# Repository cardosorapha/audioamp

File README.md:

# Amplificador de Audio

Essa é uma placa contendo um filtro passa-baixas de terceira ordem de Chebyshev com um amplificador de áudio baseado no TDA2030. No [esquemático](./Esquemático.pdf), as conexões estão descritas e separadas em blocos, que fizeram parte do projeto da [PCB](./PCB.pdf). Para montar o projeto, uma lista de materiais interativa está disponível [aqui](https://cardosorapha.github.io/audioamp/).

## Uso

Esse circuito recebe um sinal como entrada, dá um ganho o filtra com as seguintes especificações

* fs1 = 1200Hz
* fp1 = 4200hz
* Amin = 40dB
* Amax = 2dB
* Gcc = 0.5V/V

O sinal filtrado segue para o amplificador que suporta cargas de até 8R. 

### Alimentação

* +14V indicado por +VDC
* -14V indicado por -VDC
* GND

### Entradas

* Sinal de áudio indicado por por +SIG
* GND

### Saídas

* OUT1
* OUT2

Devem ser conectados ao speaker.

### Fabricação

Os arquivos gerber estão disponíveis na pasta [gerber](./gerber) para fabricação. 

## Customização

Pré-requisitos:
* [KiCAD](https://kicad-pcb.org/)

O projeto pode ser facilmente clonado com:
```
git clone https://github.com/cardosorapha/audioamp.git
```

Qualquer filtro passa-baixas de terceira ordem de topologia Sallen-Key pode ser implementado sem nenhuma modificação na placa, apenas nos componentes. Com isso, é possível modificar seus parâmetros facilmente, adaptando-os para a aplicação.

## Contato

Raphael Cardoso - cardosodeoliveir@gmail.com

Link do Projeto: [https://github.com/cardosorapha/audioamp](https://github.com/cardosorapha/audioamp)

# Desenvolvido na

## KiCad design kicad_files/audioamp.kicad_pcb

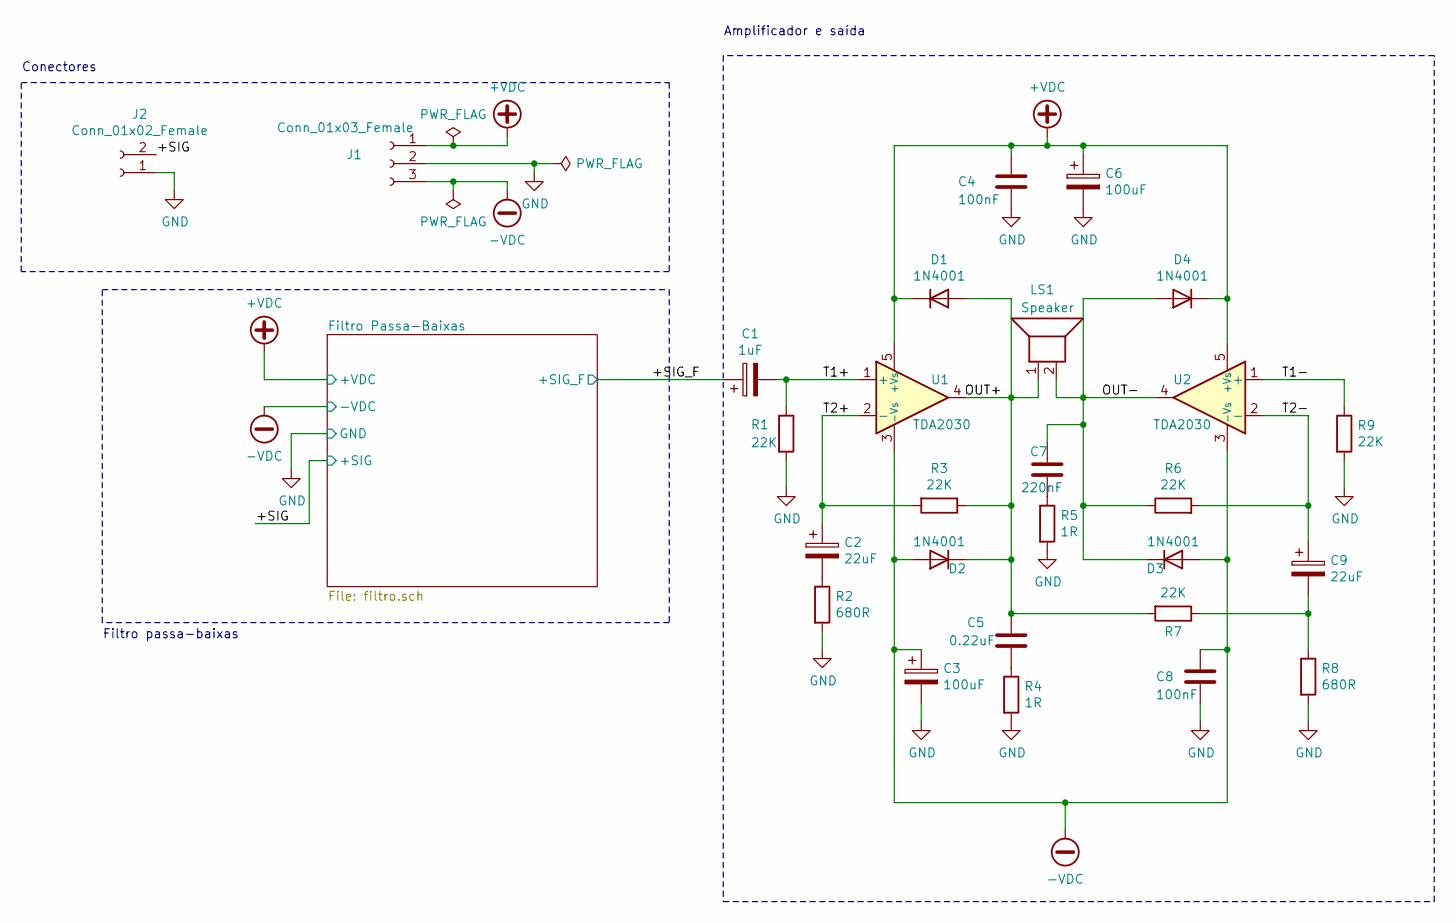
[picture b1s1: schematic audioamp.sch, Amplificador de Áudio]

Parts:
C1: 1uF; CP_Radial_D5.0mm_P2.50mm
C2, C9: 22uF; CP_Radial_D5.0mm_P2.50mm
C3, C6: 100uF; CP_Radial_D5.0mm_P2.50mm
C4, C8: 100nF; C_Disc_D4.7mm_W2.5mm_P5.00mm
C5: 0.22uF; CP_Radial_D5.0mm_P2.50mm
C7: 220nF; C_Disc_D4.7mm_W2.5mm_P5.00mm
D1, D2, D3, D4: 1N4001; D_DO-41_SOD81_P10.16mm_Horizontal
J1: Conn_01x03_Female; TerminalBlock_bornier-3_P5.08mm
J2: Conn_01x02_Female; TerminalBlock_bornier-2_P5.08mm
LS1: Speaker; TerminalBlock_bornier-2_P5.08mm
R1, R3, R6, R7, R9: 22K; R_Axial_DIN0207_L6.3mm_D2.5mm_P7.62mm_Horizontal
R2, R8: 680R; R_Axial_DIN0207_L6.3mm_D2.5mm_P7.62mm_Horizontal
R4: 1R; R_Axial_DIN0414_L11.9mm_D4.5mm_P15.24mm_Horizontal
R5: 1R; R_Axial_DIN0309_L9.0mm_D3.2mm_P12.70mm_Horizontal
U1, U2: TDA2030; TO-220-5_P3.4x3.7mm_StaggerOdd_Lead3.8mm_Vertical

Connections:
+VDC: C4.1, C6.1, D1.1 (K), D4.1 (K), J1.1, U1.5 (+Vs), U2.5 (+Vs); also elsewhere on the board
-VDC: C3.1, C8.1, D2.2 (A), D3.2 (A), J1.3, U1.3 (-Vs), U2.3 (-Vs); also elsewhere on the board
/+SIG: J2.2; also elsewhere on the board
/+SIG_F: C1.1; also elsewhere on the board
/OUT+: C5.1, D1.2 (A), D2.1 (K), LS1.1, R3.1, R7.2, U1.4
/OUT-: C7.1, D3.1 (K), D4.2 (A), LS1.2, R6.1, U2.4
/T1+: C1.2, R1.1, U1.1 (+)
/T1-: R9.1, U2.1 (+)
/T2+: C2.1, R3.2, U1.2 (-)
/T2-: C9.1, R6.2, U2.2 (-)
GND: C3.2, C4.2, C6.2, C8.2, J1.2, J2.1, R1.2, R2.2, R4.2, R5.2, R8.2, R9.2; also elsewhere on the board
unnamed: C2.2, R2.1
unnamed: C5.2, R4.1
unnamed: C7.2, R5.1
unnamed: C9.2, R7.1, R8.1

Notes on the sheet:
Conectores
Filtro passa-baixas
Amplificador e saída

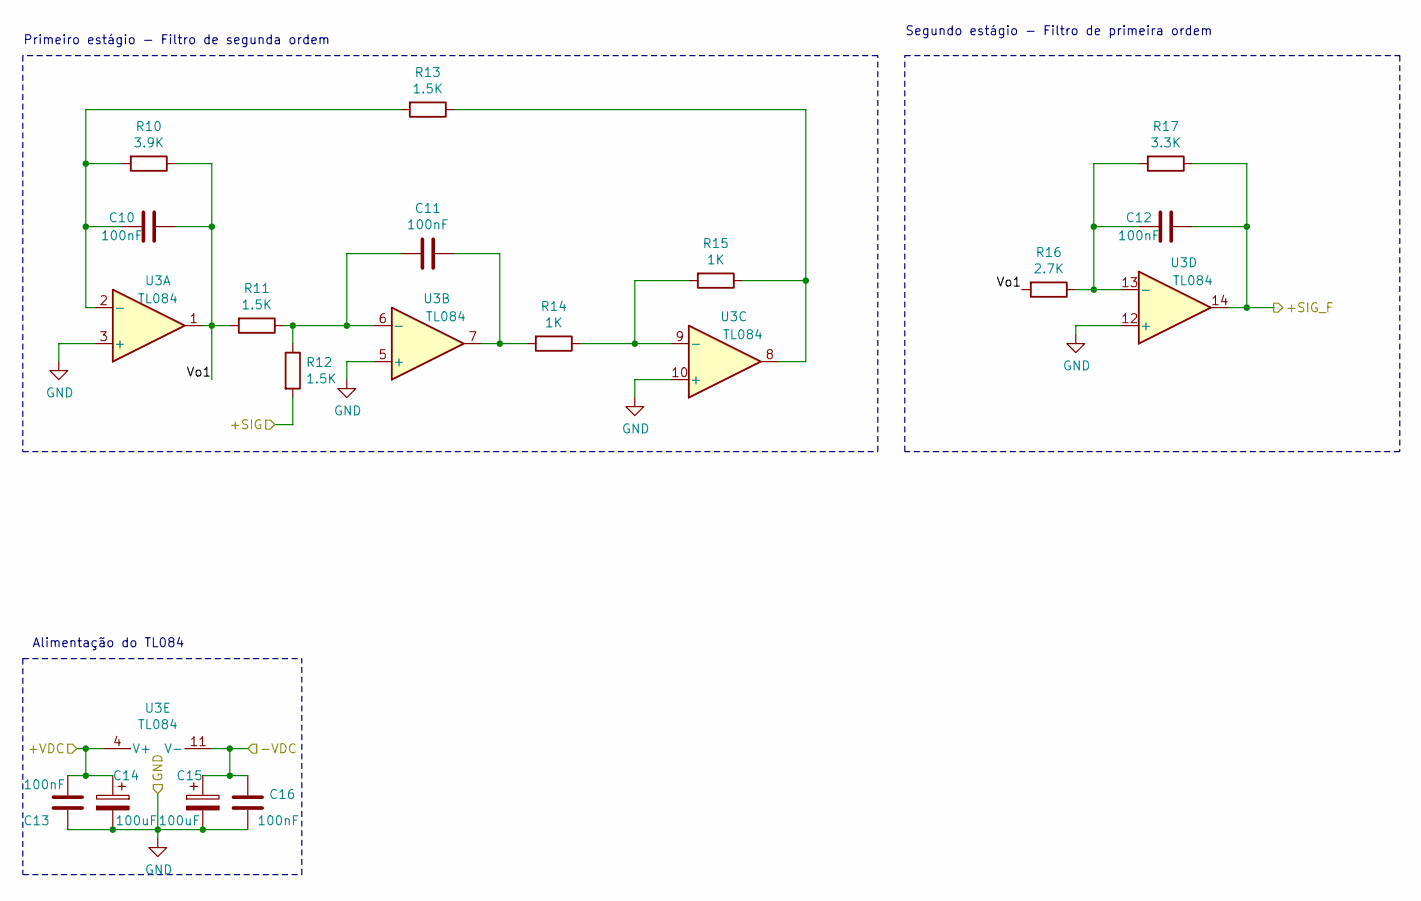
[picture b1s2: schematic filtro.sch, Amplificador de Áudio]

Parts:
C10, C11, C12, C13, C16: 100nF; C_Disc_D4.7mm_W2.5mm_P5.00mm
C14, C15: 100uF; CP_Radial_D5.0mm_P2.50mm
R10: 3.9K; R_Axial_DIN0207_L6.3mm_D2.5mm_P7.62mm_Horizontal
R11, R12, R13: 1.5K; R_Axial_DIN0207_L6.3mm_D2.5mm_P7.62mm_Horizontal
R14, R15: 1K; R_Axial_DIN0207_L6.3mm_D2.5mm_P7.62mm_Horizontal
R16: 2.7K; R_Axial_DIN0207_L6.3mm_D2.5mm_P7.62mm_Horizontal
R17: 3.3K; R_Axial_DIN0207_L6.3mm_D2.5mm_P7.62mm_Horizontal
U3: TL084; DIP-14_W7.62mm_Socket_LongPads

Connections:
+VDC: C13.1, C14.1, U3.4 (V+); also elsewhere on the board
-VDC: C15.1, C16.1, U3.11 (V-); also elsewhere on the board
/+SIG: R12.2; also elsewhere on the board
/+SIG_F: C12.1, R17.1, U3.14; also elsewhere on the board
/Filtro Passa-Baixas/Vo1: C10.1, R10.1, R11.2, R16.2, U3.1
GND: C13.2, C14.2, C15.2, C16.2, U3.3 (+), U3.5 (+), U3.10 (+), U3.12 (+); also elsewhere on the board
unnamed: C10.2, R10.2, R13.2, U3.2 (-)
unnamed: C11.1, R14.2, U3.7
unnamed: C11.2, R11.1, R12.1, U3.6 (-)
unnamed: C12.2, R16.1, R17.2, U3.13 (-)
unnamed: R13.1, R15.1, U3.8
unnamed: R14.1, R15.2, U3.9 (-)

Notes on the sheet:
Primeiro estágio - Filtro de segunda ordem
Segundo estágio - Filtro de primeira ordem
Alimentação do TL084

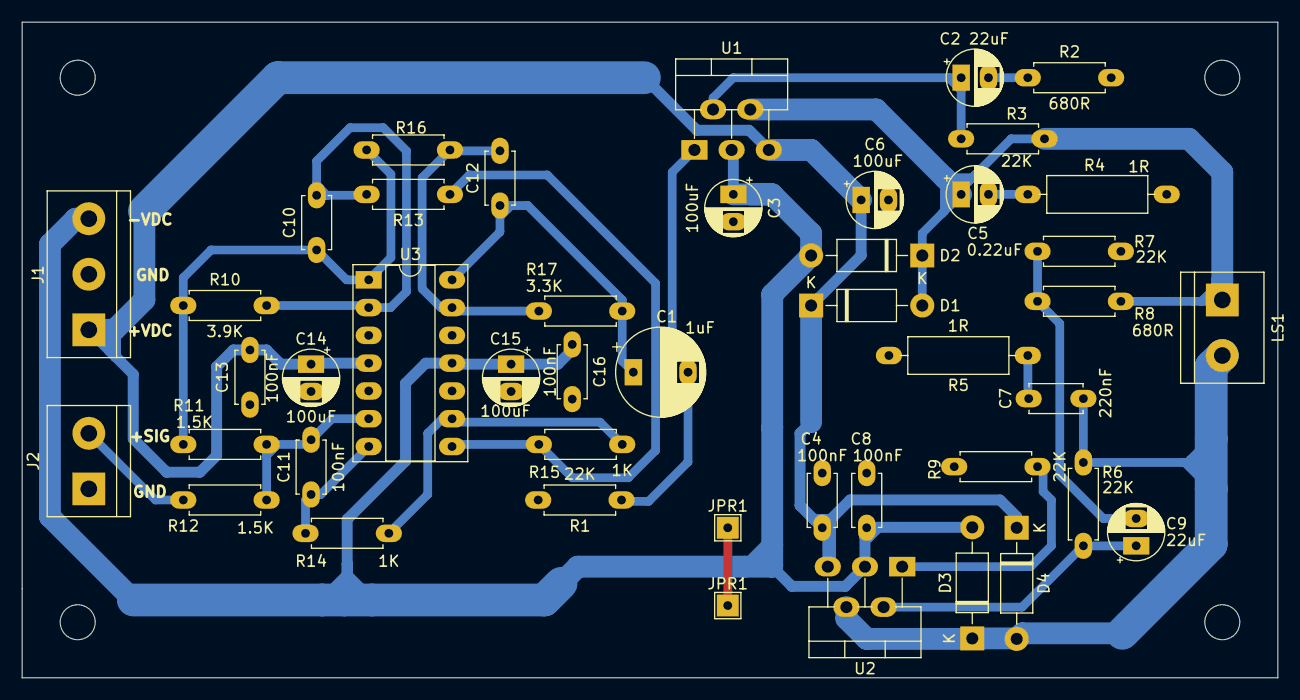
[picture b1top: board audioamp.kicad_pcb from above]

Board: 2 copper layers, 114.8 x 59.9 mm, 45 parts (0 on the bottom side), 22 nets.

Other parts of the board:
JPR1, JPR1#2: TestPoint_THTPad_2.0x2.0mm_Drill1.0mm

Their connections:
GND: JPR1.1, JPR1#2.1; also elsewhere on the board

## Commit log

2020-06-30 Criação do projeto e adição do Datasheet
2020-06-30 Componentes posicionados e anotados
2020-07-01 Amplificador conectado - Não verificado
2020-07-01 Adicionados valores do amplificador - Verificado
2020-07-01 Adicionados componentes do filtro em esquema hierárquico
2020-07-01 Colocados arquivos do esquemático do filtro
2020-07-01 Esquemático do filtro conectado e revisado
2020-07-01 Adicionados comentários e PDF gerado
2020-07-01 Adicionados footprints aos componentes
2020-07-01 Criada NETLIST
2020-07-01 Importados componentes no layout PCB e adicionados capacitores de bypass no TL084
2020-07-01 Roteado o filtro passa-baixas, 1 jumper usado
2020-07-01 Roteado o amplificador, 1 jumper usado no total
2020-07-01 Alguns componentes movidos para melhorar a organização, ainda um jumper usado
2020-07-01 Adicionados buracos de parafusos e gerados gerbers
2020-07-01 Imagens em 3D adicionadas
2020-07-01 Adicionado bill of materials
2020-07-01 Pequeno ajuste
2020-07-01 BOM como index.html para hosting do GITHUB
2020-07-02 Colocadas imagens no readme
2020-07-02 Corrigido link do esquematico
2020-07-02 Imagens editadas
2020-07-02 Adicionada imagem da UFS
2020-07-02 Trilhas engrossadas
2020-07-02 Adicionados arquivos CNC
2020-07-02 Pads mais grossos para facilitar solda
2020-07-02 Salvo projeto do flatcam
